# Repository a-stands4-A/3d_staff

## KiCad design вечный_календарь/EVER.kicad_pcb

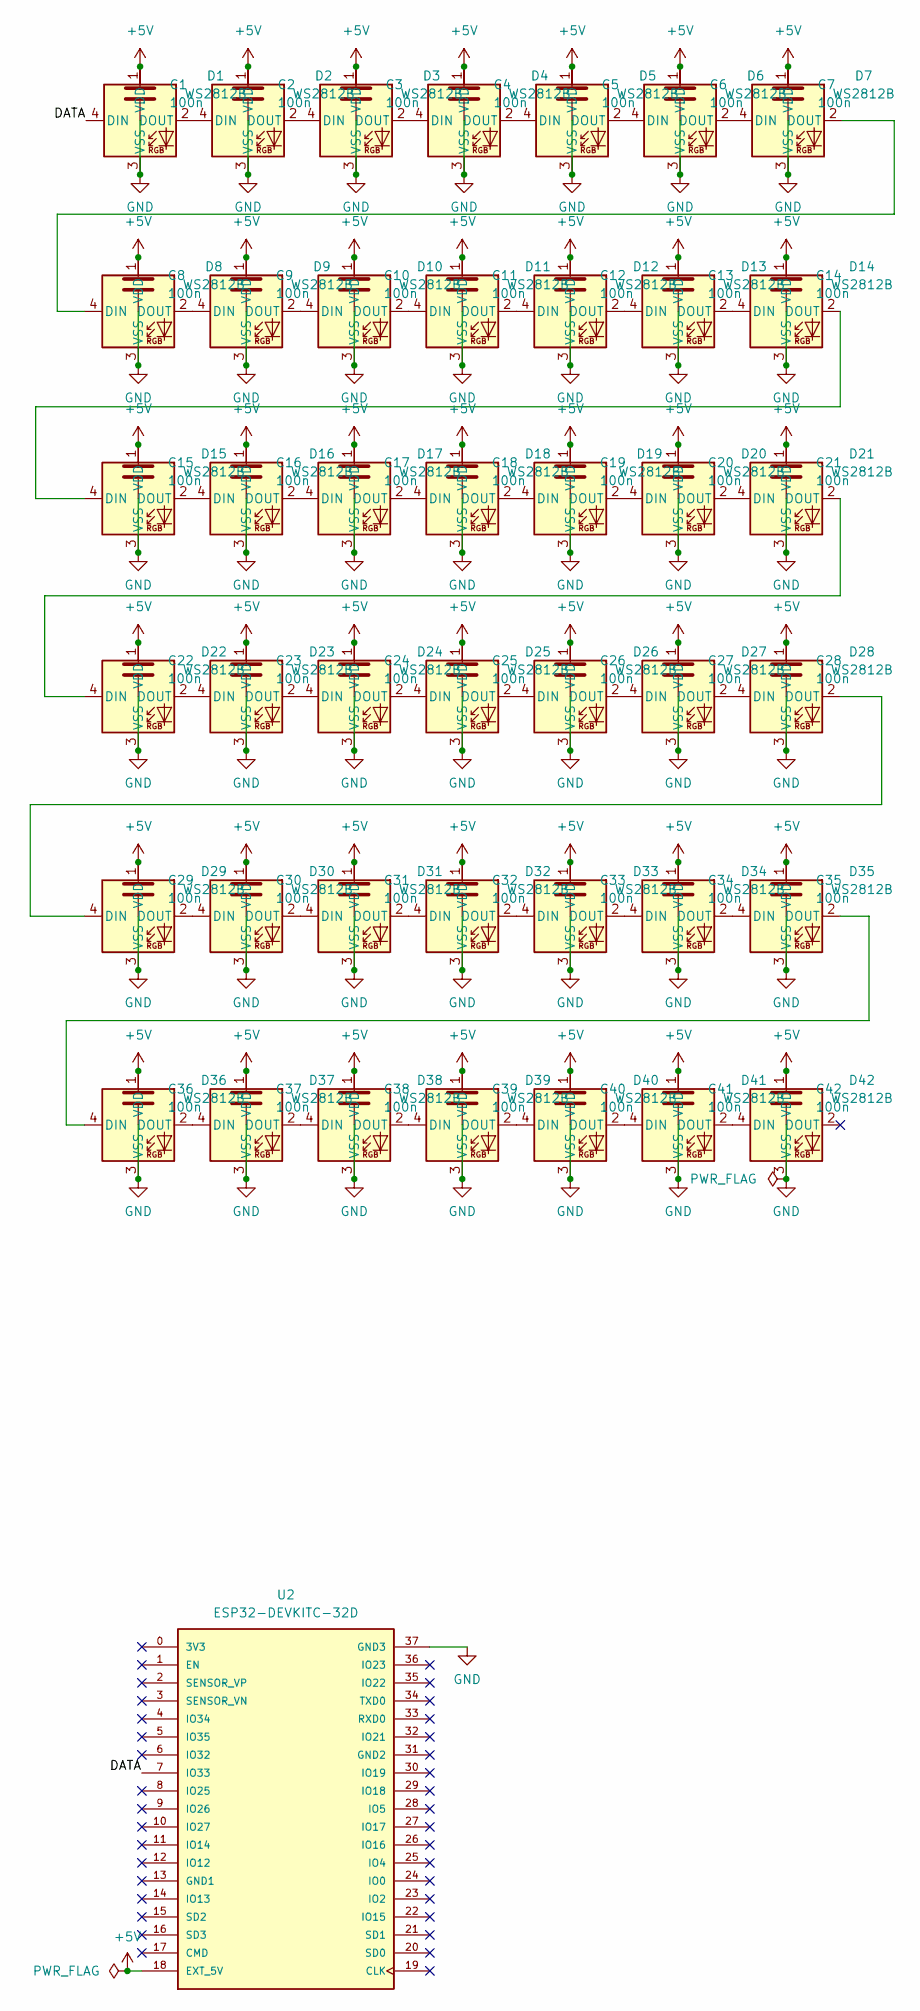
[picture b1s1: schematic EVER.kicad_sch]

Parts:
C1, C2, C3, C4, C5, C6, C7, C8, C9, C10, C11, C12, C13, C14, C15, C16, C17, C18, C19, C20, C21, C22, C23, C24, C25, C26, C27, C28, C29, C30, C31, C32, C33, C34, C35, C36, C37, C38, C39, C40, C41, C42: 100n; C_0805_2012Metric_Pad1.18x1.45mm_HandSolder
D1, D2, D3, D4, D5, D6, D7, D8, D9, D10, D11, D12, D13, D14, D15, D16, D17, D18, D19, D20, D21, D22, D23, D24, D25, D26, D27, D28, D29, D30, D31, D32, D33, D34, D35, D36, D37, D38, D39, D40, D41, D42: WS2812B; LED_WS2812B_PLCC4_5.0x5.0mm_P3.2mm
U2: ESP32-DEVKITC-32D; MODULE_ESP32-DEVKITC-32D; PARTREV V4

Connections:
+5V: C1.1, C2.1, C3.1, C4.1, C5.1, C6.1, C7.1, C8.1, C9.1, C10.1, C11.1, C12.1, C13.1, C14.1, C15.1, C16.1, C17.1, C18.1, C19.1, C20.1, C21.1, C22.1, C23.1, C24.1, C25.1, C26.1, C27.1, C28.1, C29.1, C30.1, C31.1, C32.1, C33.1, C34.1, C35.1, C36.1, C37.1, C38.1, C39.1, C40.1, C41.1, C42.1, D1.1 (VDD), D2.1 (VDD), D3.1 (VDD), D4.1 (VDD), D5.1 (VDD), D6.1 (VDD), D7.1 (VDD), D8.1 (VDD), D9.1 (VDD), D10.1 (VDD), D11.1 (VDD), D12.1 (VDD), D13.1 (VDD), D14.1 (VDD), D15.1 (VDD), D16.1 (VDD), D17.1 (VDD), D18.1 (VDD), D19.1 (VDD), D20.1 (VDD), D21.1 (VDD), D22.1 (VDD), D23.1 (VDD), D24.1 (VDD), D25.1 (VDD), D26.1 (VDD), D27.1 (VDD), D28.1 (VDD), D29.1 (VDD), D30.1 (VDD), D31.1 (VDD), D32.1 (VDD), D33.1 (VDD), D34.1 (VDD), D35.1 (VDD), D36.1 (VDD), D37.1 (VDD), D38.1 (VDD), D39.1 (VDD), D40.1 (VDD), D41.1 (VDD), D42.1 (VDD), U2.18 (EXT_5V)
/DATA: D1.4 (DIN), U2.7 (IO33)
GND: C1.2, C2.2, C3.2, C4.2, C5.2, C6.2, C7.2, C8.2, C9.2, C10.2, C11.2, C12.2, C13.2, C14.2, C15.2, C16.2, C17.2, C18.2, C19.2, C20.2, C21.2, C22.2, C23.2, C24.2, C25.2, C26.2, C27.2, C28.2, C29.2, C30.2, C31.2, C32.2, C33.2, C34.2, C35.2, C36.2, C37.2, C38.2, C39.2, C40.2, C41.2, C42.2, D1.3 (VSS), D2.3 (VSS), D3.3 (VSS), D4.3 (VSS), D5.3 (VSS), D6.3 (VSS), D7.3 (VSS), D8.3 (VSS), D9.3 (VSS), D10.3 (VSS), D11.3 (VSS), D12.3 (VSS), D13.3 (VSS), D14.3 (VSS), D15.3 (VSS), D16.3 (VSS), D17.3 (VSS), D18.3 (VSS), D19.3 (VSS), D20.3 (VSS), D21.3 (VSS), D22.3 (VSS), D23.3 (VSS), D24.3 (VSS), D25.3 (VSS), D26.3 (VSS), D27.3 (VSS), D28.3 (VSS), D29.3 (VSS), D30.3 (VSS), D31.3 (VSS), D32.3 (VSS), D33.3 (VSS), D34.3 (VSS), D35.3 (VSS), D36.3 (VSS), D37.3 (VSS), D38.3 (VSS), D39.3 (VSS), D40.3 (VSS), D41.3 (VSS), D42.3 (VSS), U2.37 (GND3)
unnamed: D1.2 (DOUT), D2.4 (DIN)
unnamed: D2.2 (DOUT), D3.4 (DIN)
unnamed: D3.2 (DOUT), D4.4 (DIN)
unnamed: D4.2 (DOUT), D5.4 (DIN)
unnamed: D5.2 (DOUT), D6.4 (DIN)
unnamed: D6.2 (DOUT), D7.4 (DIN)
unnamed: D7.2 (DOUT), D8.4 (DIN)
unnamed: D8.2 (DOUT), D9.4 (DIN)
unnamed: D9.2 (DOUT), D10.4 (DIN)
unnamed: D10.2 (DOUT), D11.4 (DIN)
unnamed: D11.2 (DOUT), D12.4 (DIN)
unnamed: D12.2 (DOUT), D13.4 (DIN)
unnamed: D13.2 (DOUT), D14.4 (DIN)
unnamed: D14.2 (DOUT), D15.4 (DIN)
unnamed: D15.2 (DOUT), D16.4 (DIN)
unnamed: D16.2 (DOUT), D17.4 (DIN)
unnamed: D17.2 (DOUT), D18.4 (DIN)
unnamed: D18.2 (DOUT), D19.4 (DIN)
unnamed: D19.2 (DOUT), D20.4 (DIN)
unnamed: D20.2 (DOUT), D21.4 (DIN)
unnamed: D21.2 (DOUT), D22.4 (DIN)
unnamed: D22.2 (DOUT), D23.4 (DIN)
unnamed: D23.2 (DOUT), D24.4 (DIN)
unnamed: D24.2 (DOUT), D25.4 (DIN)
unnamed: D25.2 (DOUT), D26.4 (DIN)
unnamed: D26.2 (DOUT), D27.4 (DIN)
unnamed: D27.2 (DOUT), D28.4 (DIN)
unnamed: D28.2 (DOUT), D29.4 (DIN)
unnamed: D29.2 (DOUT), D30.4 (DIN)
unnamed: D30.2 (DOUT), D31.4 (DIN)
unnamed: D31.2 (DOUT), D32.4 (DIN)
unnamed: D32.2 (DOUT), D33.4 (DIN)
unnamed: D33.2 (DOUT), D34.4 (DIN)
unnamed: D34.2 (DOUT), D35.4 (DIN)
unnamed: D35.2 (DOUT), D36.4 (DIN)
unnamed: D36.2 (DOUT), D37.4 (DIN)
unnamed: D37.2 (DOUT), D38.4 (DIN)
unnamed: D38.2 (DOUT), D39.4 (DIN)
unnamed: D39.2 (DOUT), D40.4 (DIN)
unnamed: D40.2 (DOUT), D41.4 (DIN)
unnamed: D41.2 (DOUT), D42.4 (DIN)

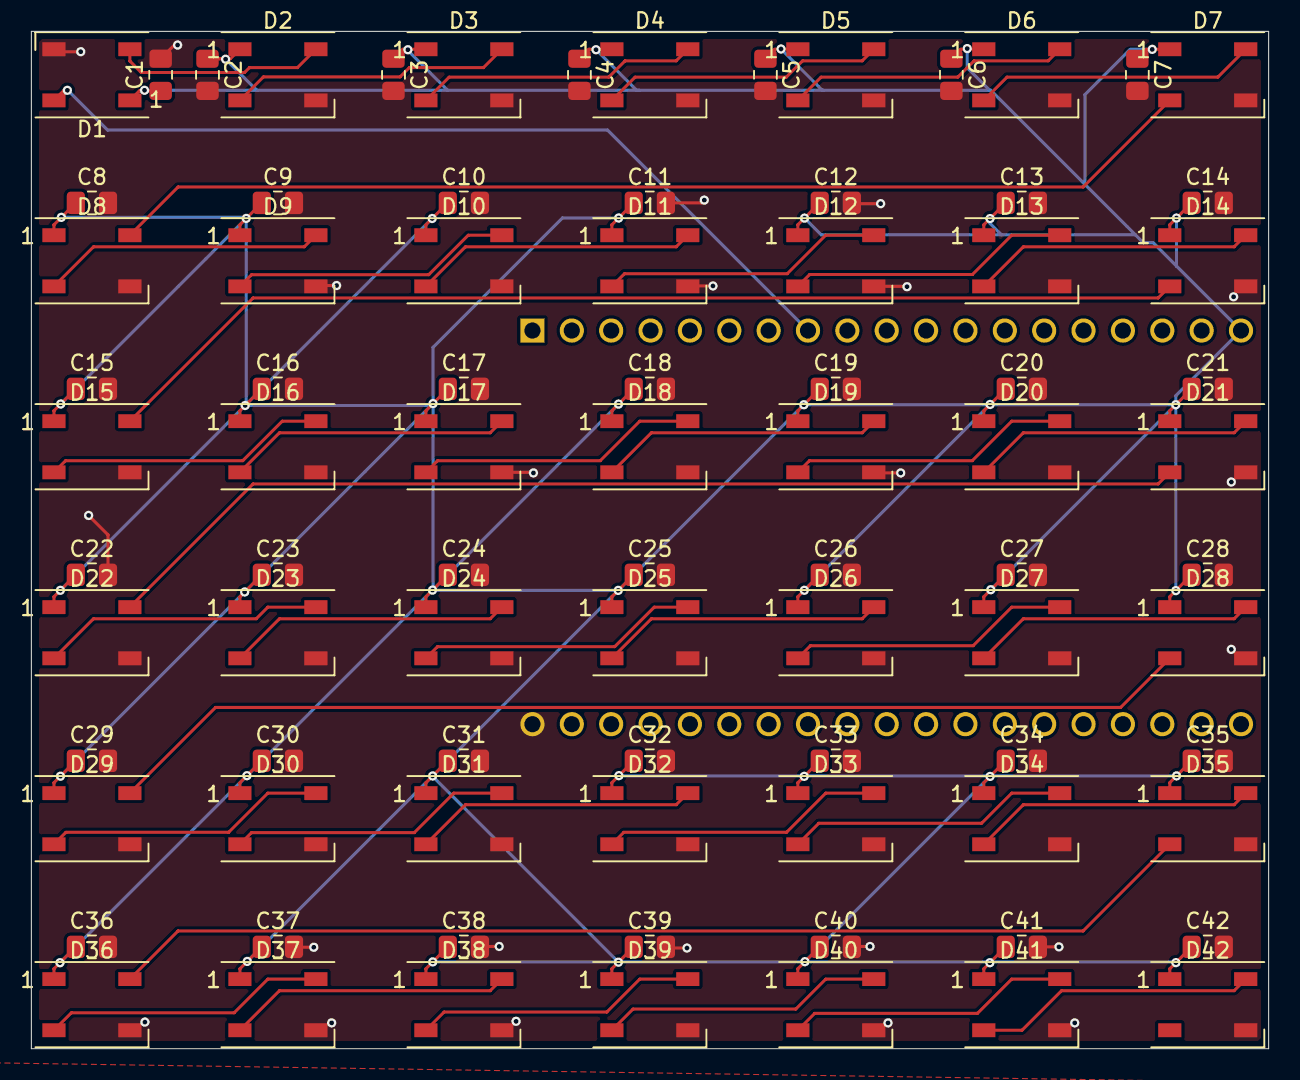
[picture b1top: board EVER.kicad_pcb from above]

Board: 2 copper layers, 79.8 x 65.6 mm, 85 parts (1 on the bottom side), 44 nets.

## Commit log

2024-06-01 nechto_stand
2024-06-02 endless_calendar
2024-06-08 endless_calendar: new stl
2024-06-17 endless_calendar: new stl; nechto: new stl
2024-06-19 nechto: new wing
2024-06-19 endless_calendar: прозрачные букавы дней добавлены
2024-07-02 endless_calendar: face changed
2024-07-02 nechto: logo on cap added
2024-07-02 nechto_stand: лишнее удалено
2024-07-12 nechto_stand: попытка увеличить устойчивость
2024-07-12 endless_calendar: минорное изменение
2024-07-21 endless_calendar: h2 -> s3 devkit; resistors added; added example for arduino code
2024-08-31 [+] card_holder added, [-] nechto turning table files
2024-08-31 sratch added
2024-08-31 part from another prj deleted
2024-08-31 src init page
2024-08-31 [-] src dir
2025-04-28 light_fountain
2025-04-28 light_fountain: STEP
